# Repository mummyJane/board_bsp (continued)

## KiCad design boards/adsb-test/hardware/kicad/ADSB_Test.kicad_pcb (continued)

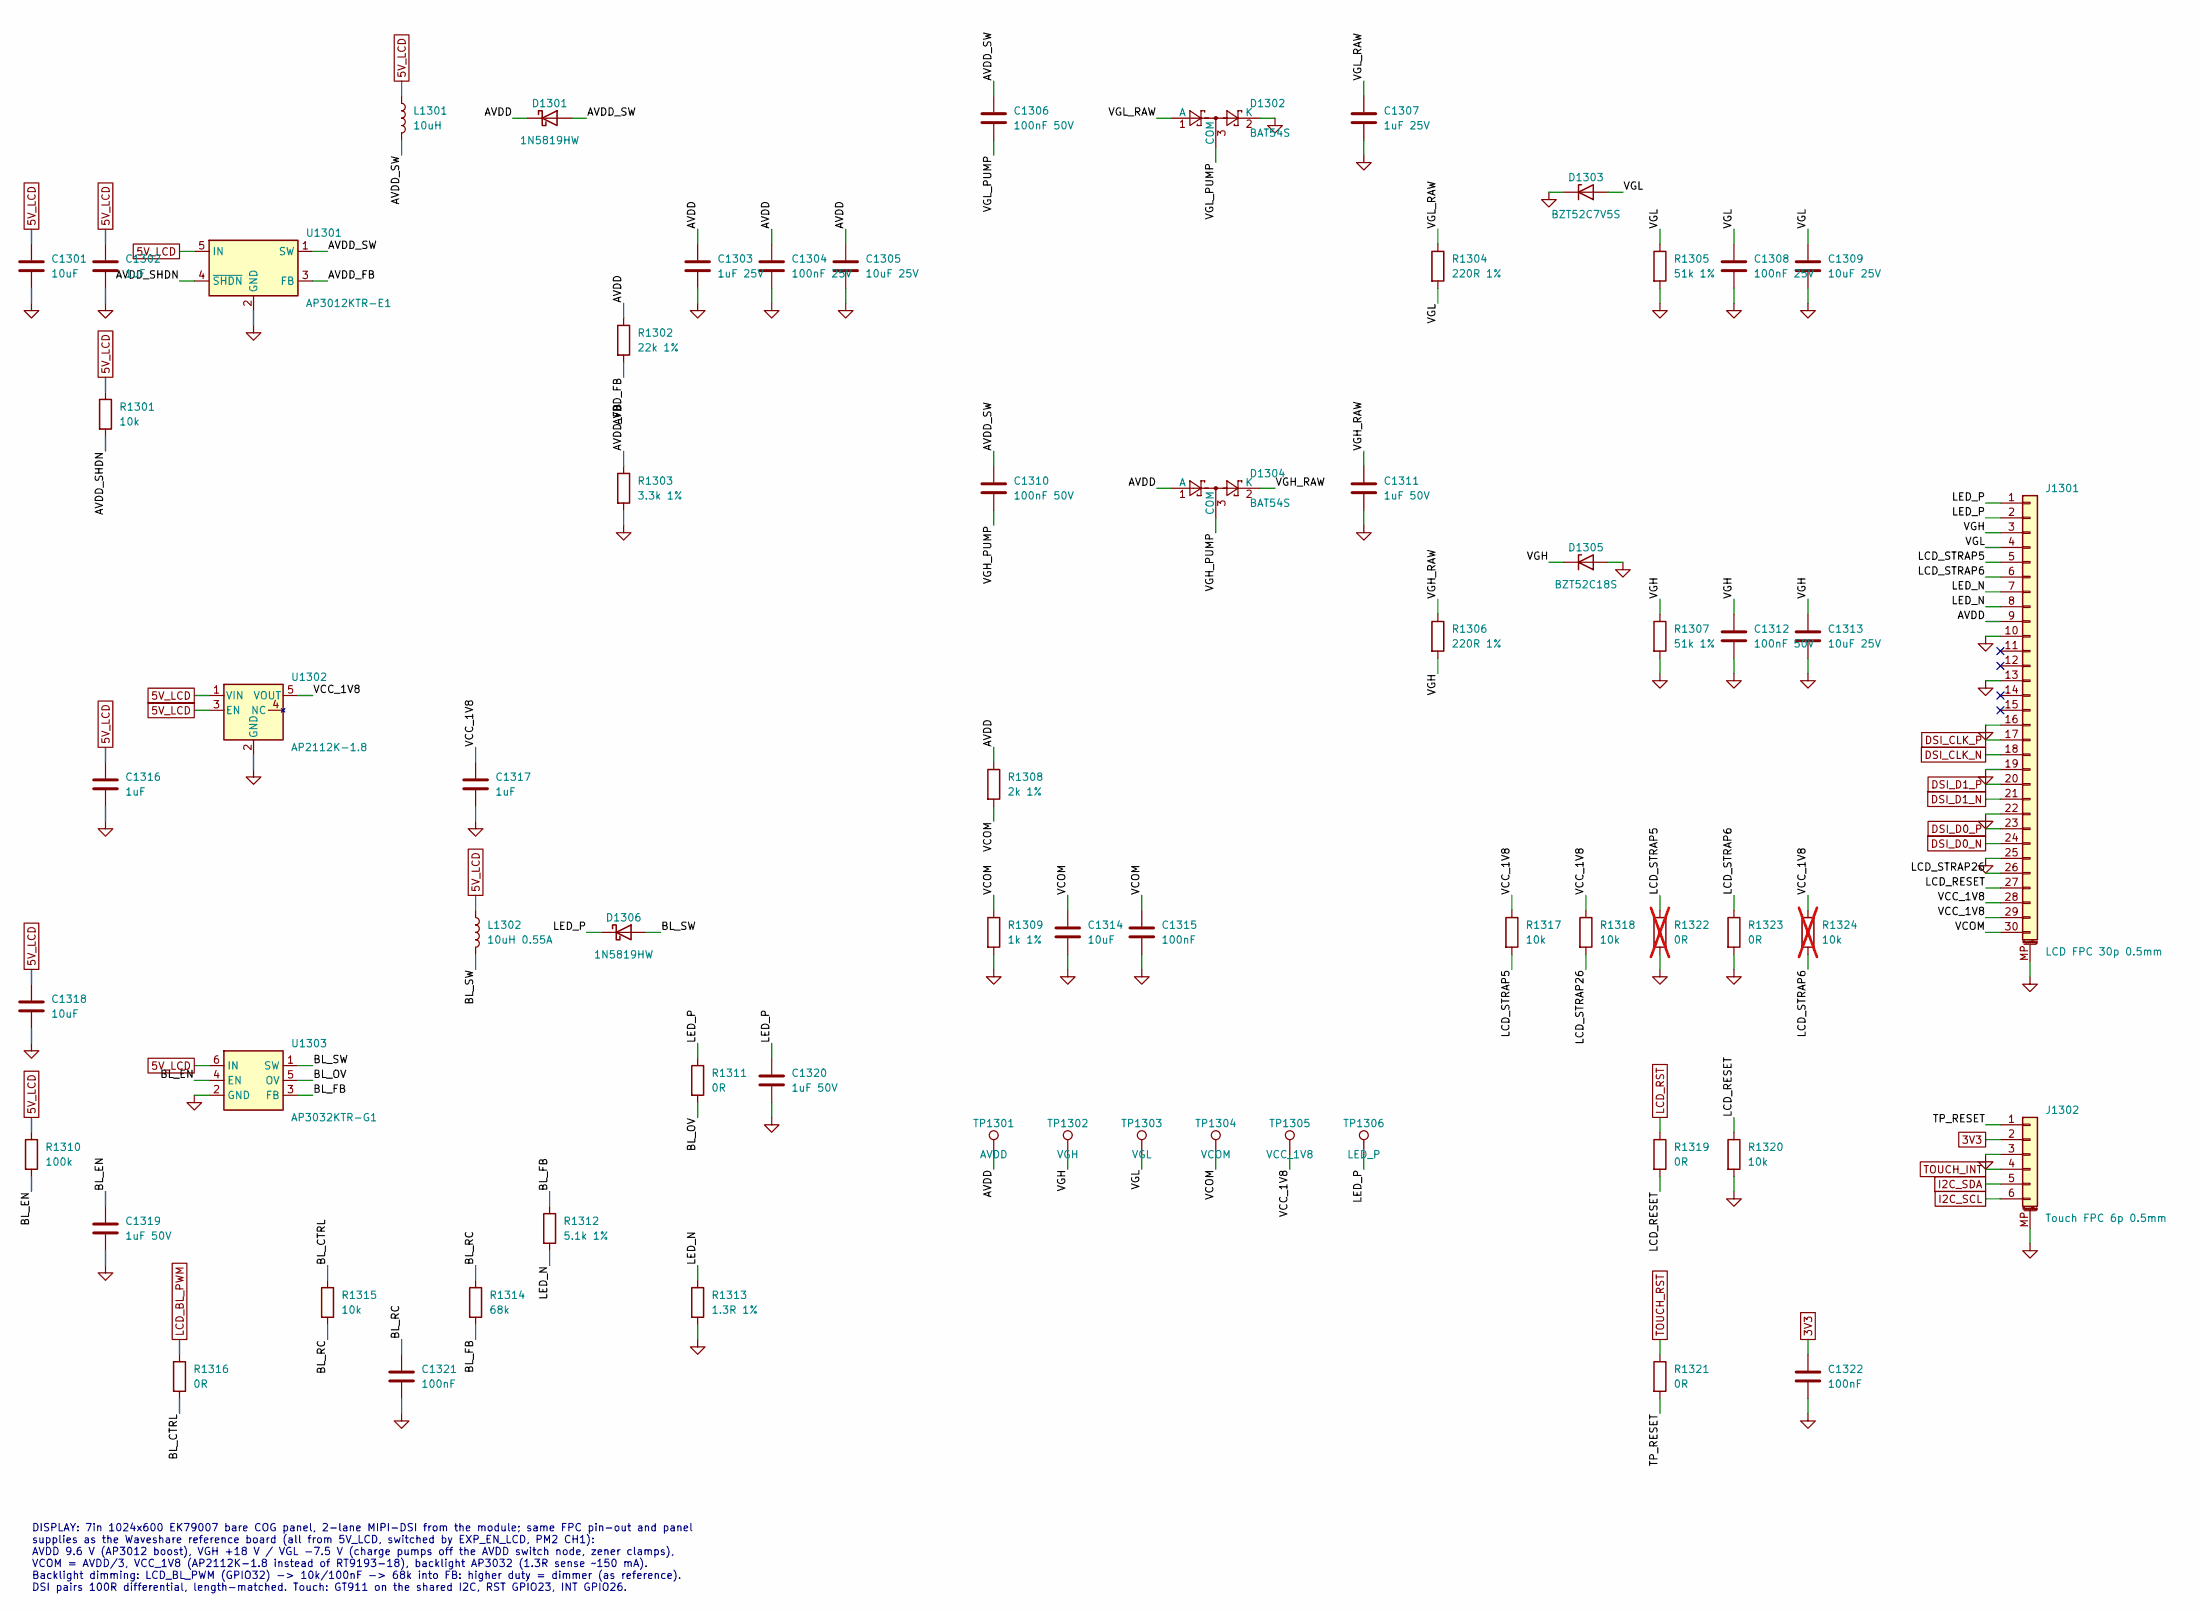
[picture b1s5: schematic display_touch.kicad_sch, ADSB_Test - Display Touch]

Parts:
C1301, C1314, C1318: 10uF; C_1206_3216Metric_Pad1.33x1.80mm_HandSolder
C1302, C1316, C1317: 1uF; C_0805_2012Metric_Pad1.18x1.45mm_HandSolder
C1303, C1307: 1uF 25V; C_0805_2012Metric_Pad1.18x1.45mm_HandSolder
C1304, C1308: 100nF 25V; C_0805_2012Metric_Pad1.18x1.45mm_HandSolder
C1305, C1309, C1313: 10uF 25V; C_1206_3216Metric_Pad1.33x1.80mm_HandSolder
C1306, C1310, C1312: 100nF 50V; C_0805_2012Metric_Pad1.18x1.45mm_HandSolder
C1311: 1uF 50V; C_0805_2012Metric_Pad1.18x1.45mm_HandSolder
C1315, C1321, C1322: 100nF; C_0805_2012Metric_Pad1.18x1.45mm_HandSolder
C1319, C1320: 1uF 50V; C_1206_3216Metric_Pad1.33x1.80mm_HandSolder
D1301, D1306: 1N5819HW; D_SOD-123
D1302, D1304: BAT54S; SOT-23_Handsoldering
D1303: BZT52C7V5S; D_SOD-123F
D1305: BZT52C18S; D_SOD-123F
J1301: LCD FPC 30p 0.5mm; Hirose_FH12-30S-0.5SH_1x30-1MP_P0.50mm_Horizontal
J1302: Touch FPC 6p 0.5mm; Hirose_FH12-6S-0.5SH_1x06-1MP_P0.50mm_Horizontal
L1301: 10uH; L_Bourns-SRN4018
L1302: 10uH 0.55A; L_Bourns-SRN4018
R1301, R1315, R1317, R1318, R1320: 10k; R_0805_2012Metric_Pad1.20x1.40mm_HandSolder
R1302: 22k 1%; R_0805_2012Metric_Pad1.20x1.40mm_HandSolder
R1303: 3.3k 1%; R_0805_2012Metric_Pad1.20x1.40mm_HandSolder
R1304, R1306: 220R 1%; R_0805_2012Metric_Pad1.20x1.40mm_HandSolder
R1305, R1307: 51k 1%; R_0805_2012Metric_Pad1.20x1.40mm_HandSolder
R1308: 2k 1%; R_0805_2012Metric_Pad1.20x1.40mm_HandSolder
R1309: 1k 1%; R_0805_2012Metric_Pad1.20x1.40mm_HandSolder
R1310: 100k; R_0805_2012Metric_Pad1.20x1.40mm_HandSolder
R1311, R1316, R1319, R1321, R1323: 0R; R_0805_2012Metric_Pad1.20x1.40mm_HandSolder
R1312: 5.1k 1%; R_0805_2012Metric_Pad1.20x1.40mm_HandSolder
R1313: 1.3R 1%; R_1206_3216Metric_Pad1.30x1.75mm_HandSolder
R1314: 68k; R_0805_2012Metric_Pad1.20x1.40mm_HandSolder
R1322: 0R; R_0805_2012Metric_Pad1.20x1.40mm_HandSolder; not fitted
R1324: 10k; R_0805_2012Metric_Pad1.20x1.40mm_HandSolder; not fitted
TP1301: AVDD; TestPoint_Pad_D1.5mm
TP1302: VGH; TestPoint_Pad_D1.5mm
TP1303: VGL; TestPoint_Pad_D1.5mm
TP1304: VCOM; TestPoint_Pad_D1.5mm
TP1305: VCC_1V8; TestPoint_Pad_D1.5mm
TP1306: LED_P; TestPoint_Pad_D1.5mm
U1301: AP3012KTR-E1; SOT-23-5_HandSoldering
U1302: AP2112K-1.8; SOT-23-5_HandSoldering
U1303: AP3032KTR-G1; SOT-23-6_Handsoldering

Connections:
3V3: C1322.1, J1302.2; also elsewhere on the board
5V_LCD: C1301.1, C1302.1, C1316.1, C1318.1, L1301.1, L1302.1, R1301.1, R1310.1, U1301.5 (IN), U1302.1 (VIN), U1302.3 (EN), U1303.6 (IN); also elsewhere on the board
/Display Touch/AVDD: C1303.1, C1304.1, C1305.1, D1301.1 (K), D1304.1 (A), J1301.9, R1302.1, R1308.1, TP1301.1
/Display Touch/AVDD_FB: R1302.2, R1303.1, U1301.3 (FB)
/Display Touch/AVDD_SHDN: R1301.2, U1301.4 (~SHDN)
/Display Touch/AVDD_SW: C1306.1, C1310.1, D1301.2 (A), L1301.2, U1301.1 (SW)
/Display Touch/BL_CTRL: R1315.1, R1316.2
/Display Touch/BL_EN: C1319.1, R1310.2, U1303.4 (EN)
/Display Touch/BL_FB: R1312.1, R1314.2, U1303.3 (FB)
/Display Touch/BL_OV: R1311.2, U1303.5 (OV)
/Display Touch/BL_RC: C1321.1, R1314.1, R1315.2
/Display Touch/BL_SW: D1306.2 (A), L1302.2, U1303.1 (SW)
/Display Touch/LCD_RESET: J1301.27, R1319.2, R1320.1
/Display Touch/LCD_STRAP5: J1301.5, R1317.2, R1322.1
/Display Touch/LCD_STRAP6: J1301.6, R1323.1, R1324.2
/Display Touch/LCD_STRAP26: J1301.26, R1318.2
/Display Touch/LED_N: J1301.7, J1301.8, R1312.2, R1313.1
/Display Touch/LED_P: C1320.1, D1306.1 (K), J1301.1, J1301.2, R1311.1, TP1306.1
/Display Touch/TP_RESET: J1302.1, R1321.2
/Display Touch/VCC_1V8: C1317.1, J1301.28, J1301.29, R1317.1, R1318.1, R1324.1, TP1305.1, U1302.5 (VOUT)
/Display Touch/VCOM: C1314.1, C1315.1, J1301.30, R1308.2, R1309.1, TP1304.1
/Display Touch/VGH: C1312.1, C1313.1, D1305.1 (K), J1301.3, R1306.2, R1307.1, TP1302.1
/Display Touch/VGH_PUMP: C1310.2, D1304.3 (COM)
/Display Touch/VGH_RAW: C1311.1, D1304.2 (K), R1306.1
/Display Touch/VGL: C1308.1, C1309.1, D1303.2 (A), J1301.4, R1304.2, R1305.1, TP1303.1
/Display Touch/VGL_PUMP: C1306.2, D1302.3 (COM)
/Display Touch/VGL_RAW: C1307.1, D1302.1 (A), R1304.1
DSI_CLK_N: J1301.18; also elsewhere on the board
DSI_CLK_P: J1301.17; also elsewhere on the board
DSI_D0_N: J1301.24; also elsewhere on the board
DSI_D0_P: J1301.23; also elsewhere on the board
DSI_D1_N: J1301.21; also elsewhere on the board
DSI_D1_P: J1301.20; also elsewhere on the board
GND: C1301.2, C1302.2, C1303.2, C1304.2, C1305.2, C1307.2, C1308.2, C1309.2, C1311.2, C1312.2, C1313.2, C1314.2, C1315.2, C1316.2, C1317.2, C1318.2, C1319.2, C1320.2, C1321.2, C1322.2, D1302.2 (K), D1303.1 (K), D1305.2 (A), J1301.10, J1301.13, J1301.16, J1301.19, J1301.22, J1301.25, J1301.MP (MountPin), J1302.3, J1302.MP (MountPin), R1303.2, R1305.2, R1307.2, R1309.2, R1313.2, R1320.2, R1322.2, R1323.2, U1301.2 (GND), U1302.2 (GND), U1303.2 (GND); also elsewhere on the board
I2C_SCL: J1302.6; also elsewhere on the board
I2C_SDA: J1302.5; also elsewhere on the board
LCD_BL_PWM: R1316.1; also elsewhere on the board
LCD_RST: R1319.1; also elsewhere on the board
TOUCH_INT: J1302.4; also elsewhere on the board
TOUCH_RST: R1321.1; also elsewhere on the board

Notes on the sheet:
DISPLAY: 7in 1024x600 EK79007 bare COG panel, 2-lane MIPI-DSI from the module; same FPC pin-out and panel supplies as the Waveshare reference board (all from 5V_LCD, switched by EXP_EN_LCD, PM2 CH1): AVDD 9.6 V (AP3012 boost), VGH +18 V / VGL -7.5 V (charge pumps off the AVDD switch node, zener cla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

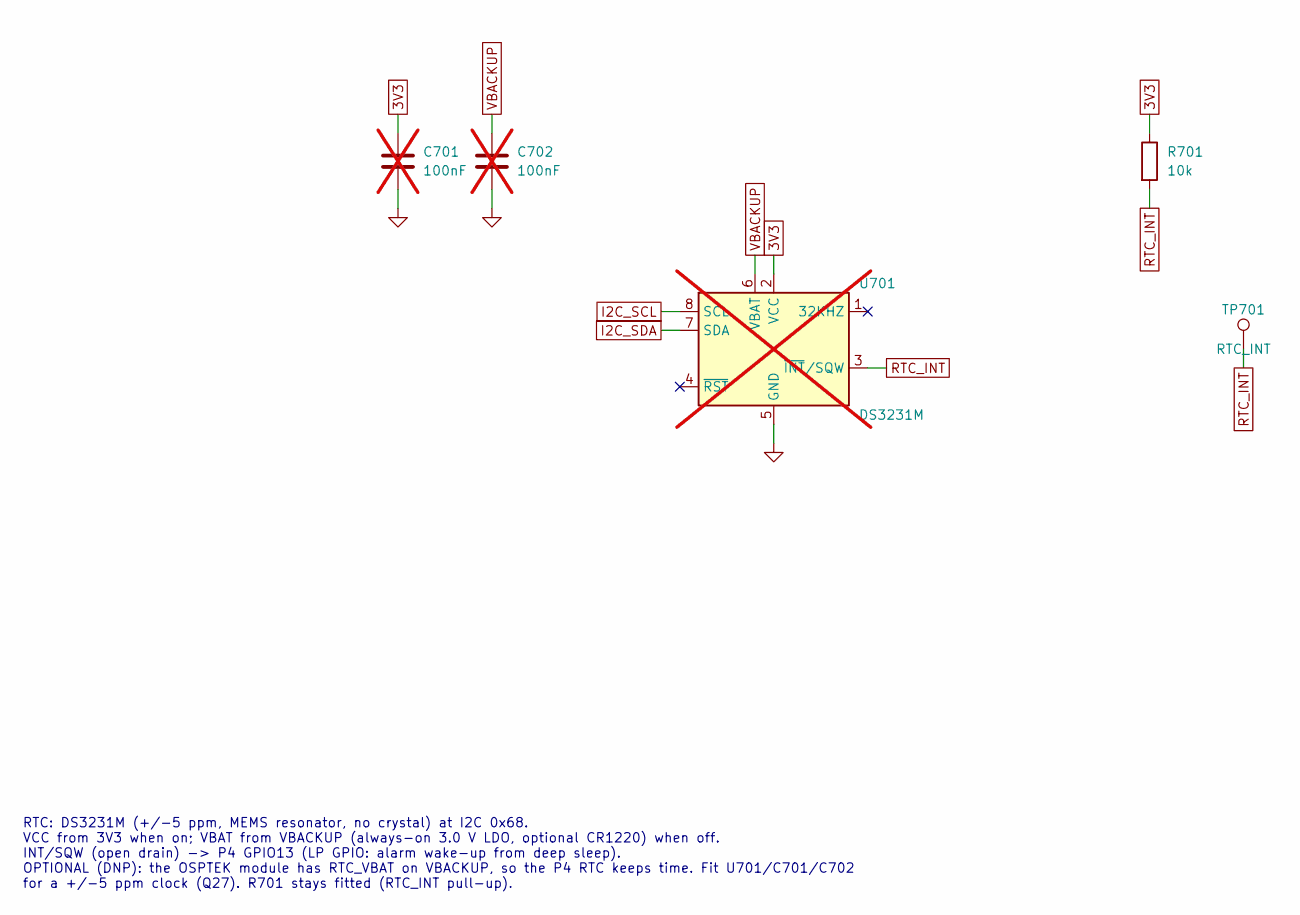
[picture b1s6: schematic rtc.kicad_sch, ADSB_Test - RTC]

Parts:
C701, C702: 100nF; C_0805_2012Metric_Pad1.18x1.45mm_HandSolder; not fitted
R701: 10k; R_0805_2012Metric_Pad1.20x1.40mm_HandSolder
TP701: RTC_INT; TestPoint_Pad_D1.5mm
U701: DS3231M; SOIC-8_3.9x4.9mm_P1.27mm; MPN DS3231MZ+; not fitted

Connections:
3V3: C701.1, R701.1, U701.2 (VCC); also elsewhere on the board
GND: C701.2, C702.2, U701.5 (GND); also elsewhere on the board
I2C_SCL: U701.8 (SCL); also elsewhere on the board
I2C_SDA: U701.7 (SDA); also elsewhere on the board
RTC_INT: R701.2, TP701.1, U701.3 (~INT/SQW); also elsewhere on the board
VBACKUP: C702.1, U701.6 (VBAT); also elsewhere on the board

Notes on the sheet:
RTC: DS3231M (+/-5 ppm, MEMS resonator, no crystal) at I2C 0x68. VCC from 3V3 when on; VBAT from VBACKUP (always-on 3.0 V LDO, optional CR1220) when off. INT/SQW (open drain) -> P4 GPIO13 (LP GPIO: alarm wake-up from deep sleep). OPTIONAL (DNP): the OSPTEK module has RTC_VBAT on VBACKUP, so the P4 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

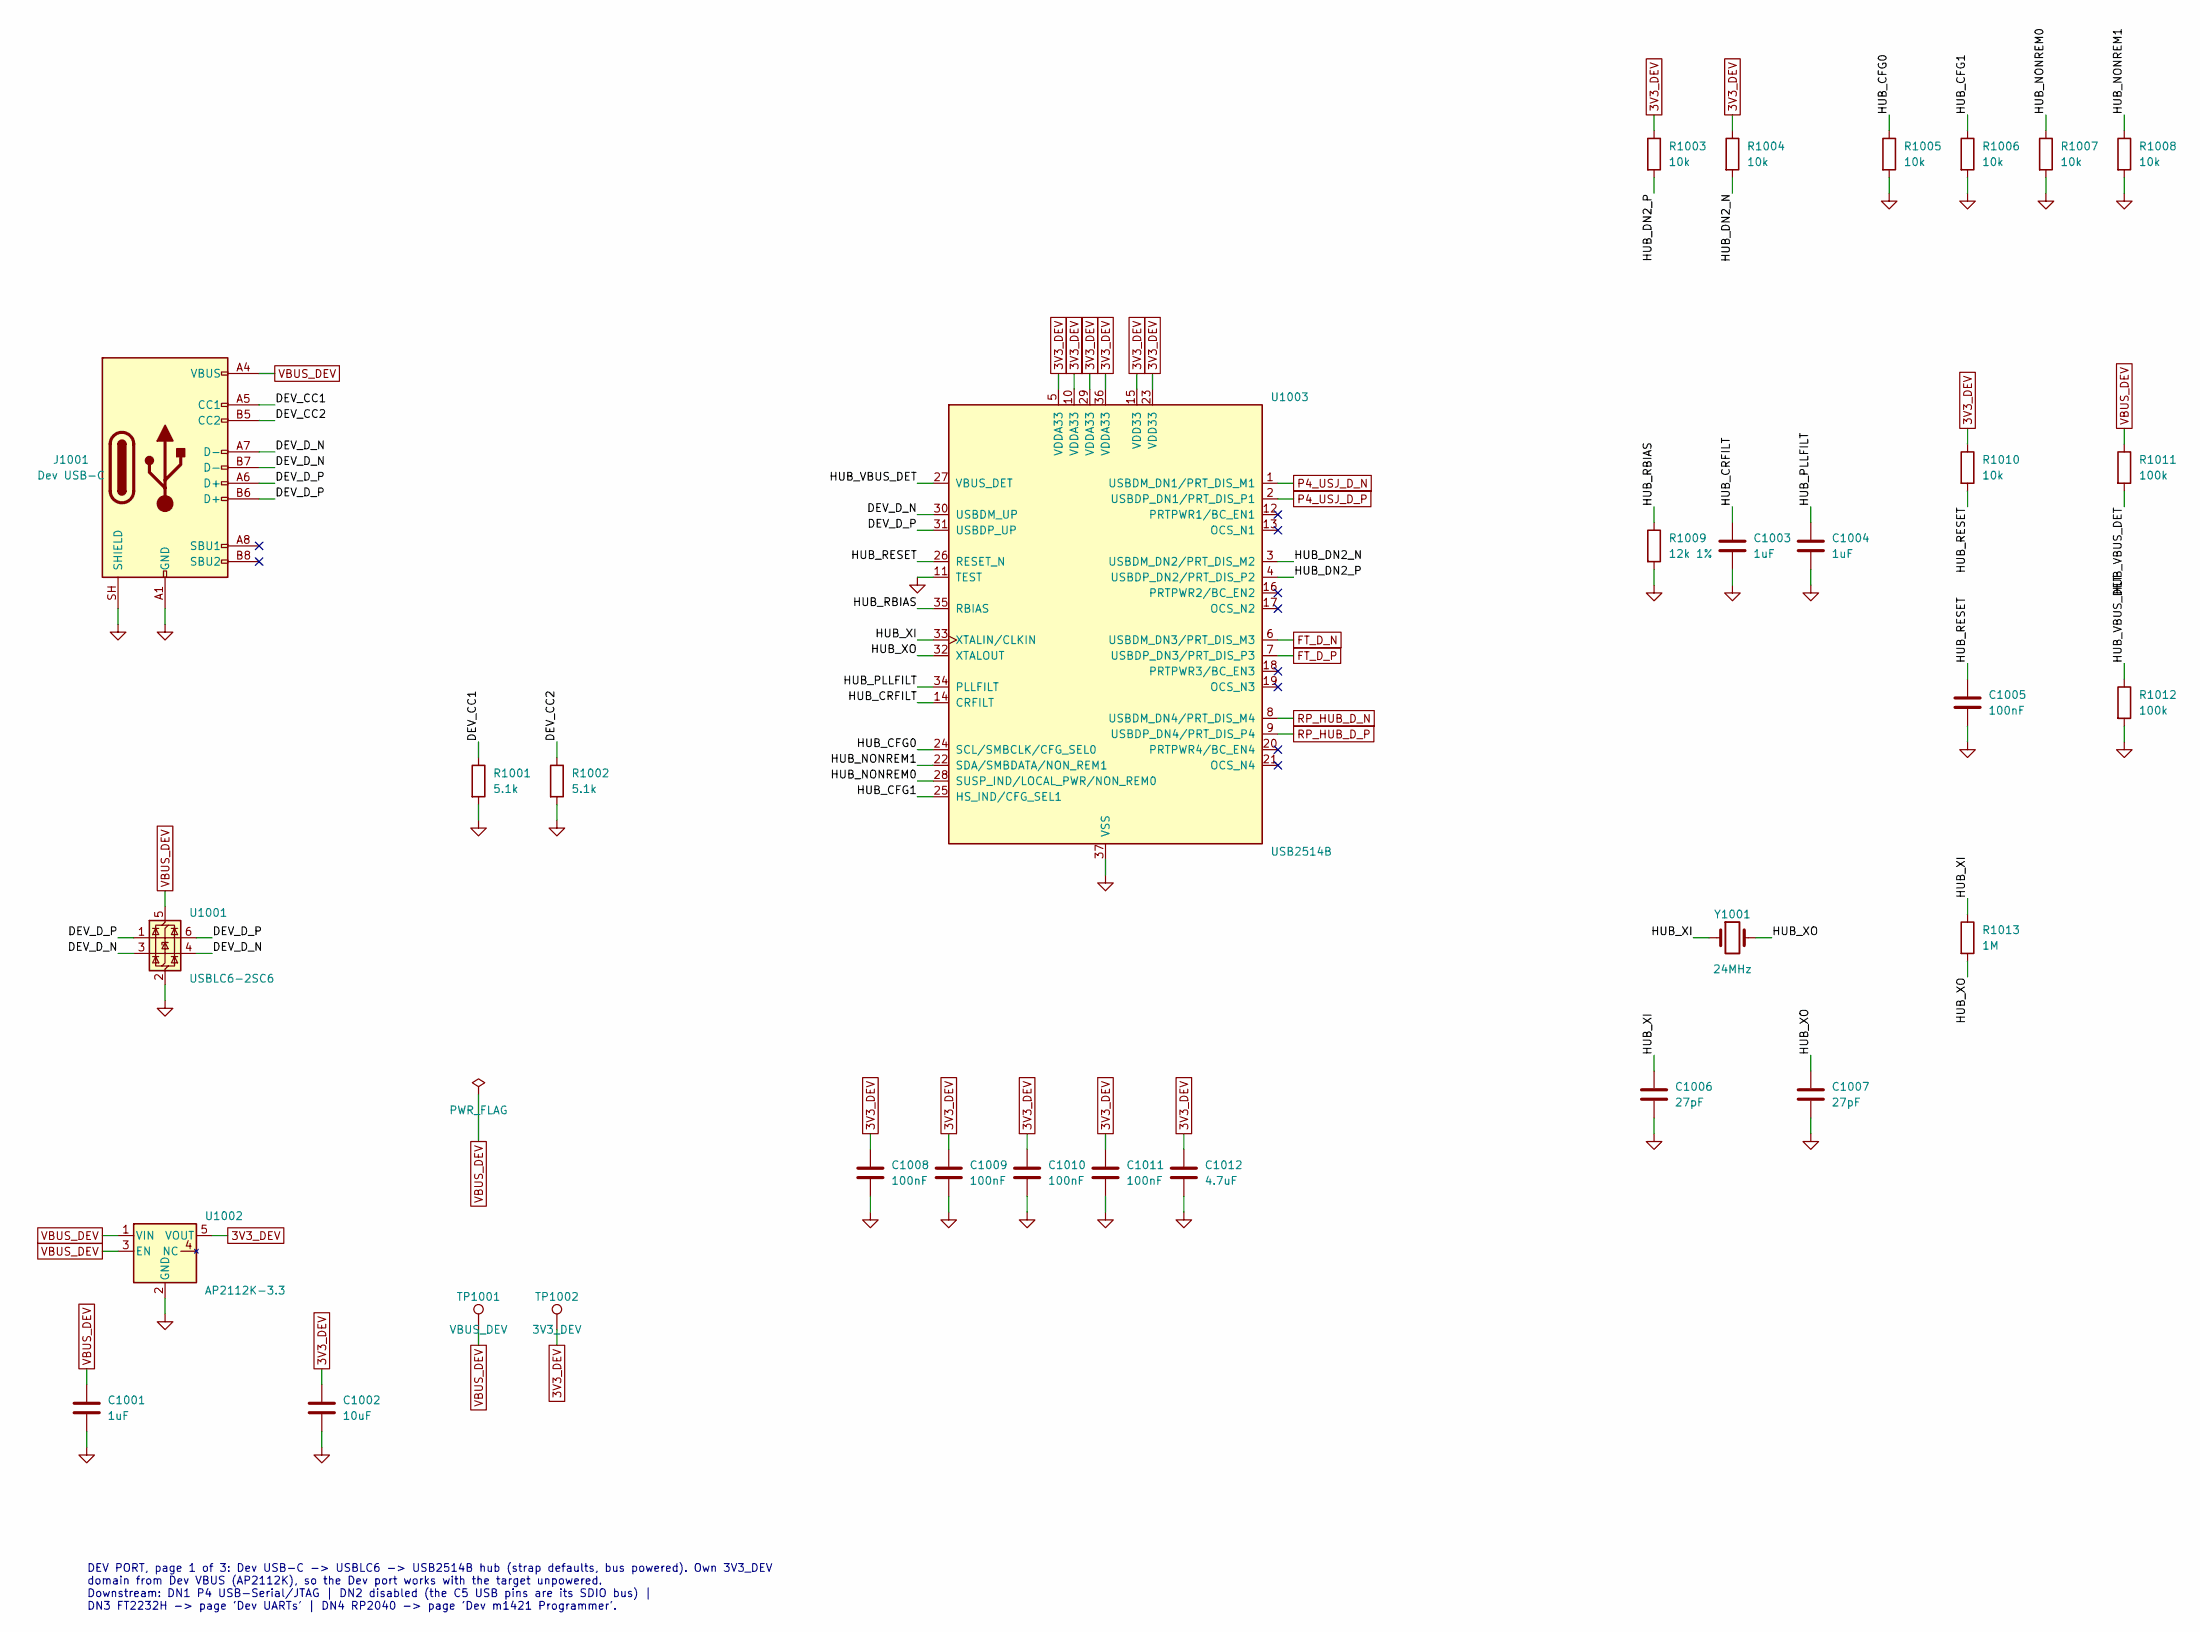
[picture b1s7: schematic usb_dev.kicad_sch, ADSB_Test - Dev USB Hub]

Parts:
C1001, C1003, C1004: 1uF; C_0805_2012Metric_Pad1.18x1.45mm_HandSolder
C1002: 10uF; C_1206_3216Metric_Pad1.33x1.80mm_HandSolder
C1005, C1008, C1009, C1010, C1011: 100nF; C_0805_2012Metric_Pad1.18x1.45mm_HandSolder
C1006, C1007: 27pF; C_0805_2012Metric_Pad1.18x1.45mm_HandSolder
C1012: 4.7uF; C_0805_2012Metric_Pad1.18x1.45mm_HandSolder
J1001: Dev USB-C; USB_C_Receptacle_GCT_USB4105-xx-A_16P_TopMnt_Horizontal
R1001, R1002: 5.1k; R_0805_2012Metric_Pad1.20x1.40mm_HandSolder
R1003, R1004, R1005, R1006, R1007, R1008, R1010: 10k; R_0805_2012Metric_Pad1.20x1.40mm_HandSolder
R1009: 12k 1%; R_0805_2012Metric_Pad1.20x1.40mm_HandSolder
R1011, R1012: 100k; R_0805_2012Metric_Pad1.20x1.40mm_HandSolder
R1013: 1M; R_0805_2012Metric_Pad1.20x1.40mm_HandSolder
TP1001: VBUS_DEV; TestPoint_Pad_D1.5mm
TP1002: 3V3_DEV; TestPoint_Pad_D1.5mm
U1001: USBLC6-2SC6; SOT-23-6_Handsoldering
U1002: AP2112K-3.3; SOT-23-5_HandSoldering
U1003: USB2514B; QFN-36-1EP_6x6mm_P0.5mm_EP3.7x3.7mm_HandSolder
Y1001: 24MHz; Crystal_SMD_5032-2Pin_5.0x3.2mm_HandSoldering

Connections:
3V3_DEV: C1002.1, C1008.1, C1009.1, C1010.1, C1011.1, C1012.1, R1003.1, R1004.1, R1010.1, TP1002.1, U1002.5 (VOUT), U1003.5 (VDDA33), U1003.10 (VDDA33), U1003.15 (VDD33), U1003.23 (VDD33), U1003.29 (VDDA33), U1003.36 (VDDA33); also elsewhere on the board
/Dev USB Hub/DEV_CC1: J1001.A5 (CC1), R1001.1
/Dev USB Hub/DEV_CC2: J1001.B5 (CC2), R1002.1
/Dev USB Hub/DEV_D_N: J1001.A7 (D-), J1001.B7 (D-), U1001.3 (I/O2), U1001.4 (I/O2), U1003.30 (USBDM_UP)
/Dev USB Hub/DEV_D_P: J1001.A6 (D+), J1001.B6 (D+), U1001.1 (I/O1), U1001.6 (I/O1), U1003.31 (USBDP_UP)
/Dev USB Hub/HUB_CFG0: R1005.1, U1003.24 (SCL/SMBCLK/CFG_SEL0)
/Dev USB Hub/HUB_CFG1: R1006.1, U1003.25 (HS_IND/CFG_SEL1)
/Dev USB Hub/HUB_CRFILT: C1003.1, U1003.14 (CRFILT)
/Dev USB Hub/HUB_DN2_N: R1004.2, U1003.3 (USBDM_DN2/PRT_DIS_M2)
/Dev USB Hub/HUB_DN2_P: R1003.2, U1003.4 (USBDP_DN2/PRT_DIS_P2)
/Dev USB Hub/HUB_NONREM0: R1007.1, U1003.28 (SUSP_IND/LOCAL_PWR/NON_REM0)
/Dev USB Hub/HUB_NONREM1: R1008.1, U1003.22 (SDA/SMBDATA/NON_REM1)
/Dev USB Hub/HUB_PLLFILT: C1004.1, U1003.34 (PLLFILT)
/Dev USB Hub/HUB_RBIAS: R1009.1, U1003.35 (RBIAS)
/Dev USB Hub/HUB_RESET: C1005.1, R1010.2, U1003.26 (RESET_N)
/Dev USB Hub/HUB_VBUS_DET: R1011.2, R1012.1, U1003.27 (VBUS_DET)
/Dev USB Hub/HUB_XI: C1006.1, R1013.1, U1003.33 (XTALIN/CLKIN), Y1001.1
/Dev USB Hub/HUB_XO: C1007.1, R1013.2, U1003.32 (XTALOUT), Y1001.2
FT_D_N: U1003.6 (USBDM_DN3/PRT_DIS_M3); also elsewhere on the board
FT_D_P: U1003.7 (USBDP_DN3/PRT_DIS_P3); also elsewhere on the board
GND: C1001.2, C1002.2, C1003.2, C1004.2, C1005.2, C1006.2, C1007.2, C1008.2, C1009.2, C1010.2, C1011.2, C1012.2, J1001.A1 (GND), J1001.A12 (GND), J1001.B1 (GND), J1001.B12 (GND), J1001.SH (SHIELD), R1001.2, R1002.2, R1005.2, R1006.2, R1007.2, R1008.2, R1009.2, R1012.2, U1001.2 (GND), U1002.2 (GND), U1003.11 (TEST), U1003.37 (VSS); also elsewhere on the board
P4_USJ_D_N: U1003.1 (USBDM_DN1/PRT_DIS_M1); also elsewhere on the board
P4_USJ_D_P: U1003.2 (USBDP_DN1/PRT_DIS_P1); also elsewhere on the board
RP_HUB_D_N: U1003.8 (USBDM_DN4/PRT_DIS_M4); also elsewhere on the board
RP_HUB_D_P: U1003.9 (USBDP_DN4/PRT_DIS_P4); also elsewhere on the board
VBUS_DEV: C1001.1, J1001.A4 (VBUS), J1001.A9 (VBUS), J1001.B4 (VBUS), J1001.B9 (VBUS), R1011.1, TP1001.1, U1001.5 (VBUS), U1002.1 (VIN), U1002.3 (EN); also elsewhere on the board

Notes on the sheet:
DEV PORT, page 1 of 3: Dev USB-C -> USBLC6 -> USB2514B hub (strap defaults, bus powered). Own 3V3_DEV domain from Dev VBUS (AP2112K), so the Dev port works with the target unpowered. Downstream: DN1 P4 USB-Serial/JTAG | DN2 disabled (the C5 USB pins are its SDIO bus) | DN3 FT2232H -> page 'Dev UART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

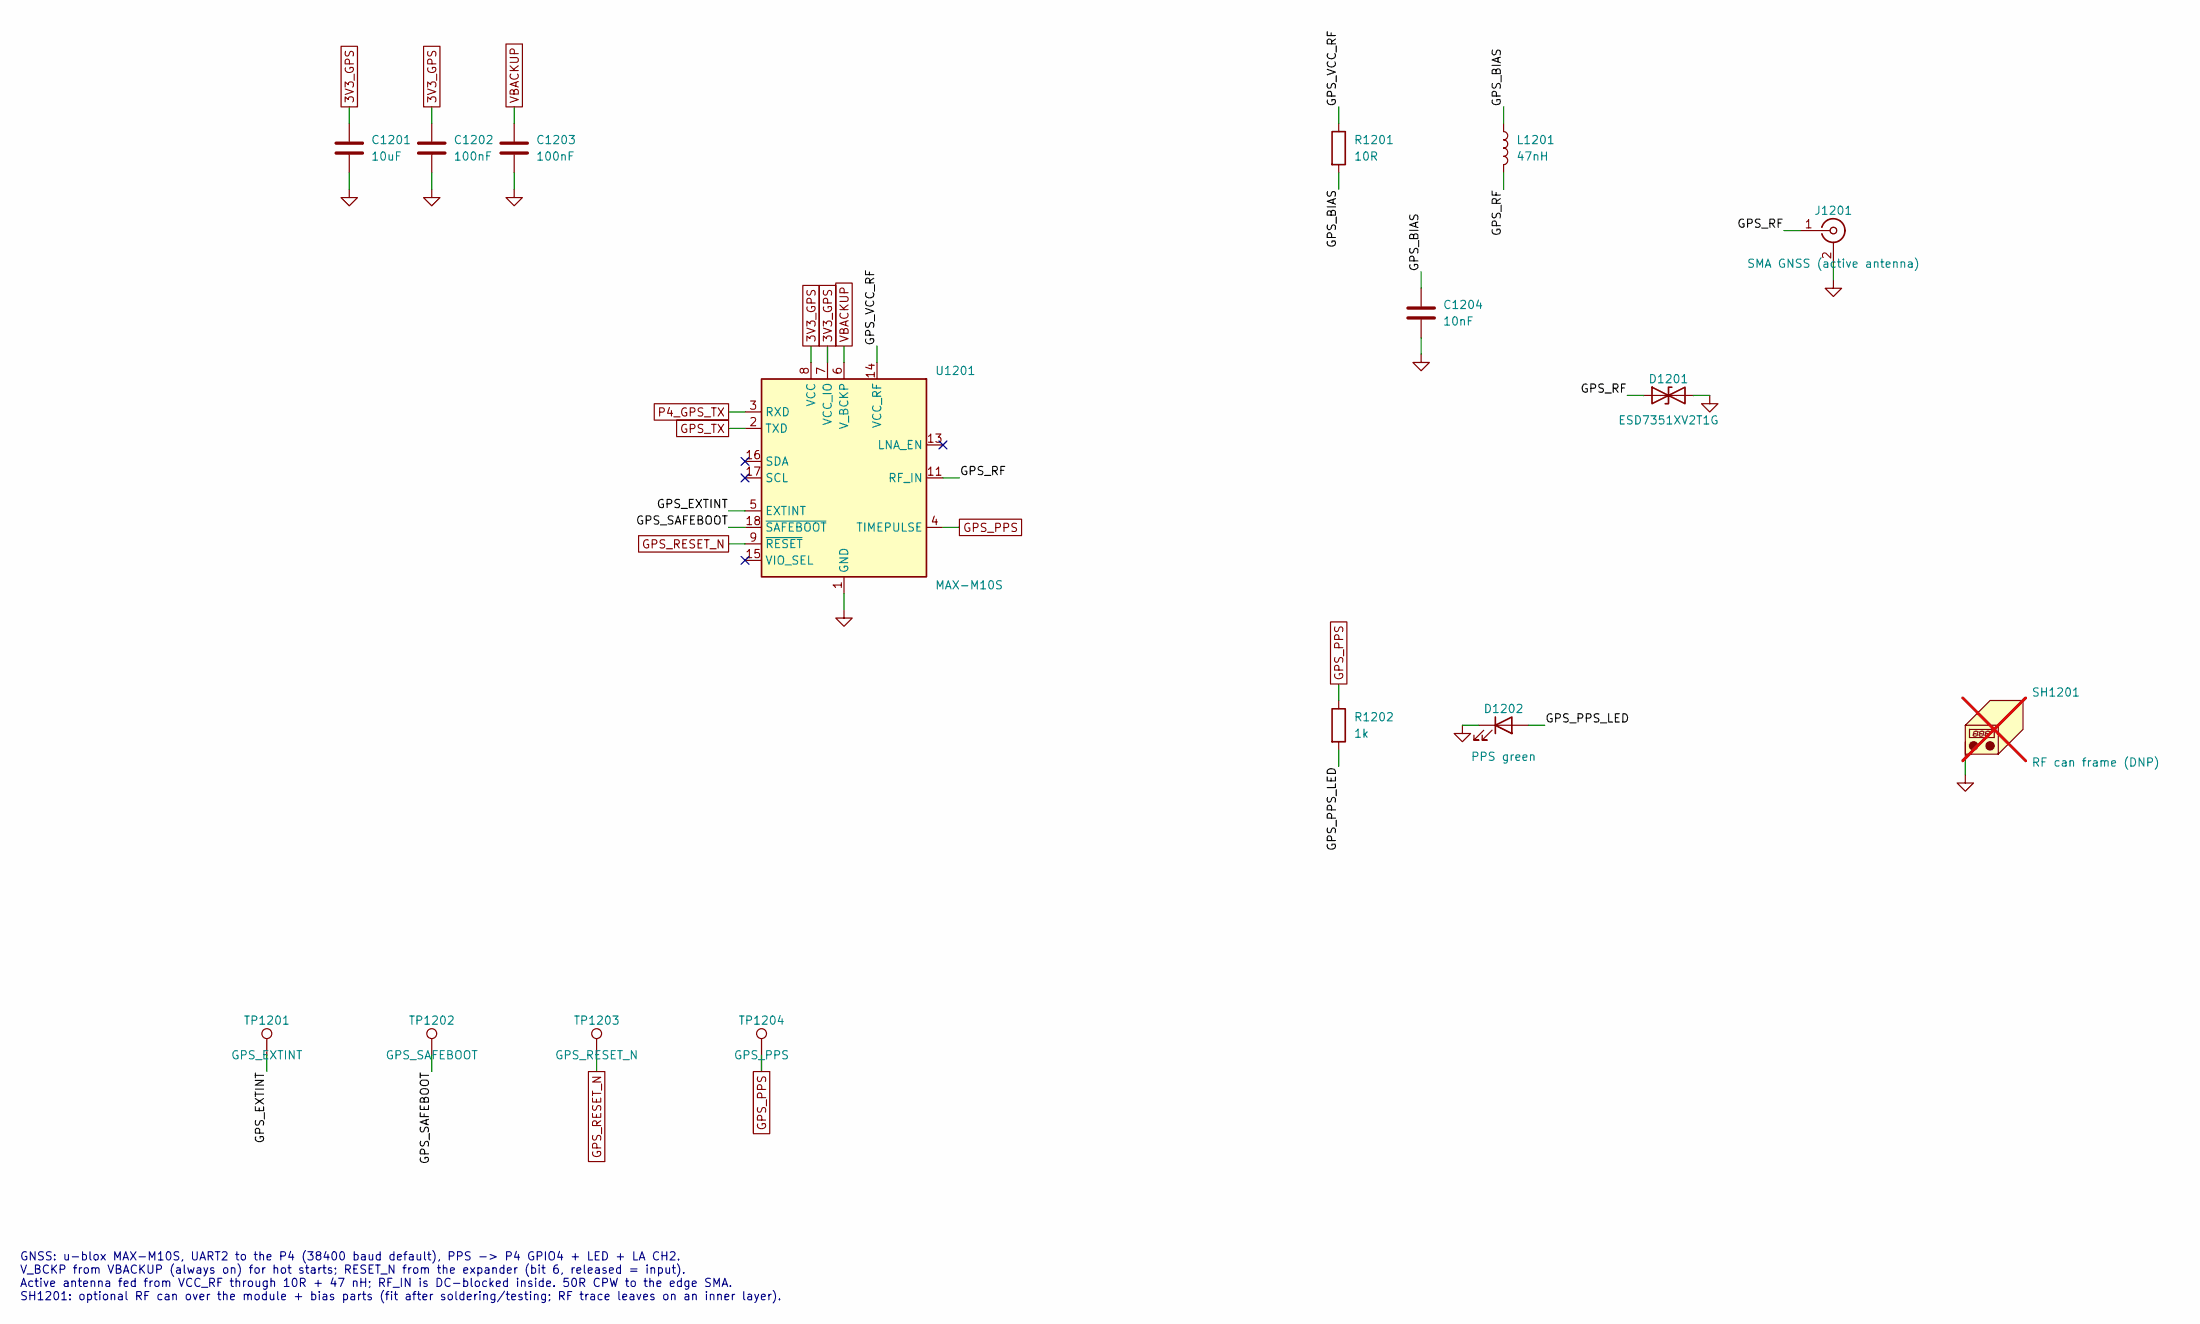
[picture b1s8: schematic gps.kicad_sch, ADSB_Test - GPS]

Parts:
C1201: 10uF; C_1206_3216Metric_Pad1.33x1.80mm_HandSolder
C1202, C1203: 100nF; C_0805_2012Metric_Pad1.18x1.45mm_HandSolder
C1204: 10nF; C_0805_2012Metric_Pad1.18x1.45mm_HandSolder
D1201: ESD7351XV2T1G; D_SOD-523
D1202: PPS green; LED_0805_2012Metric_Pad1.15x1.40mm_HandSolder
J1201: SMA GNSS (active antenna); SMA_Samtec_SMA-J-P-H-ST-EM1_EdgeMount
L1201: 47nH; L_0805_2012Metric_Pad1.05x1.20mm_HandSolder
R1201: 10R; R_0805_2012Metric_Pad1.20x1.40mm_HandSolder
R1202: 1k; R_0805_2012Metric_Pad1.20x1.40mm_HandSolder
SH1201: RF can frame (DNP); Laird_Technologies_BMI-S-202-F_16.50x16.50mm; MPN Laird BMI-S-202-F frame + BMI-S-202-C l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; not fitted
TP1201: GPS_EXTINT; TestPoint_Pad_D1.5mm
TP1202: GPS_SAFEBOOT; TestPoint_Pad_D1.5mm
TP1203: GPS_RESET_N; TestPoint_Pad_D1.5mm
TP1204: GPS_PPS; TestPoint_Pad_D1.5mm
U1201: MAX-M10S; ublox_MAX

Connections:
3V3_GPS: C1201.1, C1202.1, U1201.7 (VCC_IO), U1201.8 (VCC); also elsewhere on the board
/GPS/GPS_BIAS: C1204.1, L1201.1, R1201.2
/GPS/GPS_EXTINT: TP1201.1, U1201.5 (EXTINT)
/GPS/GPS_PPS_LED: D1202.2 (A), R1202.2
/GPS/GPS_RF: D1201.1 (A1), J1201.1 (In), L1201.2, U1201.11 (RF_IN)
/GPS/GPS_SAFEBOOT: TP1202.1, U1201.18 (~SAFEBOOT)
/GPS/GPS_VCC_RF: R1201.1, U1201.14 (VCC_RF)
GND: C1201.2, C1202.2, C1203.2, C1204.2, D1201.2 (A2), D1202.1 (K), J1201.2 (Ext), SH1201.1, U1201.1 (GND), U1201.10 (GND), U1201.12 (GND); also elsewhere on the board
GPS_PPS: R1202.1, TP1204.1, U1201.4 (TIMEPULSE); also elsewhere on the board
GPS_RESET_N: TP1203.1, U1201.9 (~RESET); also elsewhere on the board
GPS_TX: U1201.2 (TXD); also elsewhere on the board
P4_GPS_TX: U1201.3 (RXD); also elsewhere on the board
VBACKUP: C1203.1, U1201.6 (V_BCKP); also elsewhere on the board

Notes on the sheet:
GNSS: u-blox MAX-M10S, UART2 to the P4 (38400 baud default), PPS -> P4 GPIO4 + LED + LA CH2. V_BCKP from VBACKUP (always on) for hot starts; RESET_N from the expander (bit 6, released = input). Active antenna fed from VCC_RF through 10R + 47 nH; RF_IN is DC-blocked inside. 50R CPW to the edge SMA. 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

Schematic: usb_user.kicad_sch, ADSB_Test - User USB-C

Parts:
C901: 1uF; C_0805_2012Metric_Pad1.18x1.45mm_HandSolder
C902: 100nF; C_0805_2012Metric_Pad1.18x1.45mm_HandSolder
C903: 10uF 25V; C_0805_2012Metric_Pad1.18x1.45mm_HandSolder
D901: TX green; LED_0805_2012Metric_Pad1.15x1.40mm_HandSolder
D902: RX yellow; LED_0805_2012Metric_Pad1.15x1.40mm_HandSolder
D903: SMAJ20A; D_SMA
J901: User USB-C (PD sink + UART); USB_C_Receptacle_GCT_USB4105-xx-A_16P_TopMnt_Horizontal
R901: 22.1k; R_0805_2012Metric_Pad1.20x1.40mm_HandSolder
R902: 47.5k; R_0805_2012Metric_Pad1.20x1.40mm_HandSolder
R903: 10k; R_0805_2012Metric_Pad1.20x1.40mm_HandSolder
R904, R905: 1k; R_0805_2012Metric_Pad1.20x1.40mm_HandSolder
U901: CP2102N-A02-GQFN24; QFN-24-1EP_4x4mm_P0.5mm_EP2.6x2.6mm_HandSolder
U902: USBLC6-2SC6; SOT-23-6_Handsoldering

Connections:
3V3_PERIPH: C901.1, C902.1, R903.1, R904.1, R905.1, U901.5 (VIO), U901.6 (VDD), U901.7 (VREGIN), U902.5 (VBUS); also elsewhere on the board
/User USB-C/CP_RST: R903.2, U901.9 (~RST)
/User USB-C/CP_RXLED: D902.1 (K), U901.13 (~RXT/GPIO.1)
/User USB-C/CP_RXLED_A: D902.2 (A), R905.2
/User USB-C/CP_TXLED: D901.1 (K), U901.14 (~TXT/GPIO.0)
/User USB-C/CP_TXLED_A: D901.2 (A), R904.2
/User USB-C/CP_VBUS: R901.2, R902.1, U901.8 (VBUS)
/User USB-C/USER_D_N: J901.A7 (D-), J901.B7 (D-), U901.4 (D-), U902.3 (I/O2), U902.4 (I/O2)
/User USB-C/USER_D_P: J901.A6 (D+), J901.B6 (D+), U901.3 (D+), U902.1 (I/O1), U902.6 (I/O1)
GND: C901.2, C902.2, C903.2, D903.2 (A), J901.A1 (GND), J901.A12 (GND), J901.B1 (GND), J901.B12 (GND), J901.SH (SHIELD), R902.2, U901.2 (GND), U901.25 (GND), U902.2 (GND); also elsewhere on the board
P4_USER_RX: U901.21 (TXD); also elsewhere on the board
P4_USER_TX: U901.20 (RXD); also elsewhere on the board
USER_CC1: J901.A5 (CC1); also elsewhere on the board
USER_CC2: J901.B5 (CC2); also elsewhere on the board
VBUS_USER: R901.1; also elsewhere on the board
VBUS_USER_RAW: C903.1, D903.1 (K), J901.A4 (VBUS), J901.A9 (VBUS), J901.B4 (VBUS), J901.B9 (VBUS); also elsewhere on the board

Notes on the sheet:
USER USB-C: receptacle J901 (16-pin USB 2.0), VBUS TVS D903, data-line ESD U902. VBUS_USER_RAW and CC1/CC2 go to the STUSB4500 PD sink on the Power Input sheet. D+/D- (USB_90R pair) -> CP2102N (self-powered from 3V3_PERIPH), VBUS sense from VBUS_USER through 22.1k/47.5k. TXD/RXD to P4 UART1 (GPIO22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

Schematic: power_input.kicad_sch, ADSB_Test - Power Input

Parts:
C202, C203: 1uF; C_0805_2012Metric_Pad1.18x1.45mm_HandSolder
C204: 1uF 25V; C_0805_2012Metric_Pad1.18x1.45mm_HandSolder
C205: 10uF 25V; C_0805_2012Metric_Pad1.18x1.45mm_HandSolder
D202: SS34; D_SMA
JP201: Dev VBUS -> charger (default open); SolderJumper-2_P1.3mm_Open_RoundedPad1.0x1.5mm
Q201: FDS9435A; SOIC-8_3.9x4.9mm_P1.27mm
R201: 1k; R_0805_2012Metric_Pad1.20x1.40mm_HandSolder
R202, R204: 10k; R_0805_2012Metric_Pad1.20x1.40mm_HandSolder
R203: 100k; R_0805_2012Metric_Pad1.20x1.40mm_HandSolder
RS201: 20m; R_Shunt_1206_Kelvin_HandSolder
TP201: PD_ATTACH; TestPoint_Pad_D1.5mm
TP202: VBUS_USER; TestPoint_Pad_D1.5mm
U201: STUSB4500QTR; QFN-24-1EP_4x4mm_P0.5mm_EP2.7x2.7mm_HandSolder

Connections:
3V3_PERIPH: R204.1; also elsewhere on the board
/Power Input/DEV_VBUS_JP: D202.2 (A), JP201.2 (B)
/Power Input/PD_ATTACH: TP201.1, U201.11 (ATTACH)
/Power Input/PD_DISCH: R201.2, U201.9 (DISCH)
/Power Input/PD_GATE: Q201.4 (G), R203.2, U201.16 (VBUS_EN_SNK)
/Power Input/PD_RESET: R202.1, U201.6 (RESET)
/Power Input/PD_VREG12: C202.1, U201.21 (VREG_1V2)
/Power Input/PD_VREG27: C203.1, U201.23 (VREG_2V7)
CHG_PD_INT: R204.2, U201.19 (ALERT); also elsewhere on the board
GND: C202.2, C203.2, C204.2, C205.2, R202.2, U201.10 (GND), U201.12 (ADDR0), U201.13 (ADDR1), U201.22 (VSYS), U201.25 (GND); also elsewhere on the board
I2C_SCL: U201.7 (SCL); also elsewhere on the board
I2C_SDA: U201.8 (SDA); also elsewhere on the board
PM1_CH1_N: RS201.3; also elsewhere on the board
PM1_CH1_P: RS201.2; also elsewhere on the board
USER_CC1: U201.1 (CC1DB), U201.2 (CC1); also elsewhere on the board
USER_CC2: U201.4 (CC2), U201.5 (CC2DB); also elsewhere on the board
VBUS_CHG: D202.1 (K), RS201.4; also elsewhere on the board
VBUS_DEV: JP201.1 (A); also elsewhere on the board
VBUS_USER: C205.1, Q201.5 (D), Q201.6 (D), Q201.7 (D), Q201.8 (D), R201.1, RS201.1, TP202.1; also elsewhere on the board
VBUS_USER_RAW: C204.1, Q201.1 (S), Q201.2 (S), Q201.3 (S), R203.1, U201.18 (VBUS_VS_DISCH), U201.24 (VDD); also elsewhere on the board

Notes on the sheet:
POWER INPUT: User USB-C (on the User USB-C sheet) -> STUSB4500 PD sink (NVM: 5 V / 9 V / 15 V at 3 A, I2C 0x28). VBUS_EN_SNK drives the FDS9435A P-FET (SO-8), so VBUS_USER only appears once a contract is in place. RS201 (20 mR) -> PM1 CH1. JP201 (default open) lets the Dev USB VBUS feed the charger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

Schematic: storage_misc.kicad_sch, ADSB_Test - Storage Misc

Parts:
C1501: 10uF; C_1206_3216Metric_Pad1.33x1.80mm_HandSolder
C1502, C1503: 100nF; C_0805_2012Metric_Pad1.18x1.45mm_HandSolder
J1501: microSD (push-pull, detect); microSD_HC_Molex_104031-0811
Q1501: AO3401A; SOT-23_Handsoldering
R1501, R1502, R1503, R1504, R1505, R1506, R1507, R1508, R1509: 10k; R_0805_2012Metric_Pad1.20x1.40mm_HandSolder
R1510, R1511, R1512, R1513: 100k; R_0805_2012Metric_Pad1.20x1.40mm_HandSolder
TP1501: SD_VDD; TestPoint_Pad_D1.5mm
U1501: TCA6408APW; TSSOP-16_4.4x5mm_P0.65mm

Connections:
3V3_PERIPH: C1503.1, R1507.1, R1508.1, R1509.1, U1501.1 (V_{CCI}), U1501.16 (V_{CCP}); also elsewhere on the board
3V3_SD: Q1501.2 (S), R1506.1; also elsewhere on the board
/Storage Misc/EXP_RESET: R1508.2, U1501.3 (~RESET)
/Storage Misc/SD_DET: J1501.9 (DET_B), R1507.2, U1501.10 (P5)
/Storage Misc/SD_VDD: C1501.1, C1502.1, J1501.4 (VDD), Q1501.3 (D), TP1501.1
EXP_EN_ETH: R1511.1, U1501.5 (P1); also elsewhere on the board
EXP_EN_GPS: R1512.1, U1501.6 (P2); also elsewhere on the board
EXP_EN_LCD: R1510.1, U1501.4 (P0); also elsewhere on the board
EXP_EN_M1421: R1513.1, U1501.7 (P3); also elsewhere on the board
EXP_INT: R1509.2, U1501.13 (~INT); also elsewhere on the board
EXP_USBA_EN: U1501.9 (P4); also elsewhere on the board
GND: C1501.2, C1502.2, C1503.2, J1501.6 (VSS), J1501.10 (DET_A), J1501.SH (SHIELD), R1510.2, R1511.2, R1512.2, R1513.2, U1501.2 (ADDR), U1501.8 (GND); also elsewhere on the board
GPS_RESET_N: U1501.11 (P6); also elsewhere on the board
I2C_SCL: U1501.14 (SCL); also elsewhere on the board
I2C_SDA: U1501.15 (SDA); also elsewhere on the board
M1421_NRST: U1501.12 (P7); also elsewhere on the board
SD_CLK: J1501.5 (CLK); also elsewhere on the board
SD_CMD: J1501.3 (CMD), R1501.2; also elsewhere on the board
SD_D0: J1501.7 (DAT0), R1502.2; also elsewhere on the board
SD_D1: J1501.8 (DAT1), R1503.2; also elsewhere on the board
SD_D2: J1501.1 (DAT2), R1504.2; also elsewhere on the board
SD_D3: J1501.2 (DAT3/CD), R1505.2; also elsewhere on the board
SD_PWR_EN: Q1501.1 (G), R1506.2; also elsewhere on the board
SD_VIO: R1501.1, R1502.1, R1503.1, R1504.1, R1505.1; also elsewhere on the board

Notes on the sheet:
microSD: P4 SDMMC slot 0, 4-bit (GPIO39-44), I/O from the module's ESP_LDO_VO4 (SD_VIO), 10k pull-ups. Card power: 3V3_SD (shunt RS405, PM2 CH3) -> AO3401A, GPIO45 low = on (as reference). Detect -> expander P5. TCA6408A (0x20): P0 EN_LCD, P1 EN_ETH, P2 EN_GPS, P3 EN_M1421, P4 USBA_EN (100k pull-do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
